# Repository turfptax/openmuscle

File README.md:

# 🧠 OpenMuscle (Legacy Repository)

> 📢 **NOTE:** This repository is no longer actively maintained.  
> All current work has moved to the new [**Open-Muscle GitHub Organization**](https://github.com/Open-Muscle).  
> Please see the new [OpenMuscle Hub](https://github.com/Open-Muscle/OpenMuscle-Hub) for the latest devices, firmware, and documentation.

---

## ⚡ Quick Links to New Repositories

| Project | Description | Link |
|--------|-------------|------|
| **OpenMuscle Hub** | Central documentation and overview for all OpenMuscle projects | [OpenMuscle-Hub](https://github.com/Open-Muscle/OpenMuscle-Hub) |
| **FlexGrid** | Modular 60-sensor wearable (successor to OM12) | [OpenMuscle-FlexGrid](https://github.com/Open-Muscle/OpenMuscle-FlexGrid) |
| **LASK5** | Labeling device with joystick and buttons | [OpenMuscle-LASK5](https://github.com/Open-Muscle/OpenMuscle-LASK5) |
| **Software** | MicroPython firmware, communication protocols, and ML hooks | [OpenMuscle-Software](https://github.com/Open-Muscle/OpenMuscle-Software) |
| **OM12 Legacy Band** | Historical 12-sensor band hardware | [OpenMuscle-Band](https://github.com/Open-Muscle/OpenMuscle-Band) |

---

## 🧬 About This Repo

This was the **original prototype** of OpenMuscle (OM12 + LASK4), developed to prove out muscle-based finger tracking using off-the-shelf parts and MicroPython.

It remains here for archival purposes and for those referencing:
- Early research and design iterations
- Press and academic mentions (42+ stars)
- Explorations in UDP-based muscle telemetry using hall effect sensors

<div align="center">
    
</div>

---

## 🧪 Prototype Overview

### 🧠 OM12 – OpenMuscle 12 Sensor Band (v5.3.0)

- 12 Hall Effect Sensors (49E)
- 6 Sensor Cells, dual-input
- PCB 5.3.0
- ESP32-S2
- MicroPython
- 1200 s/s via UDP transmission

### ✋ LASK4 (Legacy)

- 4 pistons
- 4 push buttons
- OLED screen
- ESP32-S2 Microcontroller

> The latest version is [LASK5](https://github.com/Open-Muscle/OpenMuscle-LASK5), with joystick and modular controls.

---

## ✅ Legacy Roadmap (Preserved for Context)

- [x] Create an open-source forearm bracelet (OM12)
- [x] Build a hand gesture labeling device (LASK4)
- [x] Create UDP-based data capture tool
- [ ] Build a hosted data training server
- [ ] Raise community awareness
- [ ] Create pre-production versions of both devices

---

## 🧾 License

This repo remains under the MIT License, but newer repositories may use the CERN-OHL-S v2.0 for hardware components. See the respective repos for details.

---

Made with 💡 by [@TURFPTAx](https://github.com/turfptax)  
Project now maintained at [Open-Muscle](https://github.com/Open-Muscle)

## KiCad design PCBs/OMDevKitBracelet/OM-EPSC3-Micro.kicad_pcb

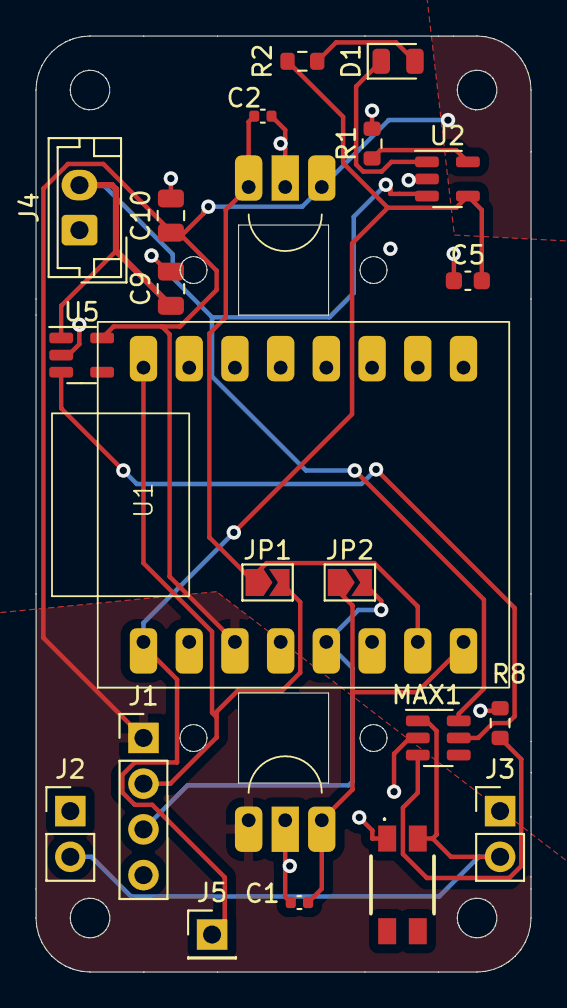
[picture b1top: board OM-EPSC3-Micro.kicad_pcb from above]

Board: 2 copper layers, 27.5 x 52.0 mm, 23 parts (0 on the bottom side), 14 nets.

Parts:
C1, C2: 100 nF; C_0402_1005Metric
C5: 2.2 uF; C_0603_1608Metric
C9, C10: 4.7uF; C_0805_2012Metric
D1: LED GREEN; LED_0805_2012Metric
H0, H1: A1369xUA-10; Hall49E
J1: Conn_01x04_Pin; PinHeader_1x04_P2.54mm_Vertical
J2, J3: Conn_01x02_Pin; PinHeader_1x02_P2.54mm_Vertical
J4: JST_02; JST_EH_B2B-EH-A_1x02_P2.50mm_Vertical
J5: Conn_01x01_Pin; PinHeader_1x01_P2.54mm_Vertical
JP1, JP2: SolderJumper_2_Open; SolderJumper-2_P1.3mm_Open_TrianglePad1.0x1.5mm
MAX1: SOT-23-6
R1: 2.7k; R_0603_1608Metric
R2: 150; R_0603_1608Metric
R8: 1K; R_0603_1608Metric
SW2: SW_Push; EVQP2P02M
U1: ESP32-C3-Super Mini
U2: LTC4054ES5-4.2; TSOT-23-5
U5: TPS7A03; SOT-23-5

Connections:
+3V3: C10.1, H0.1 (VCC), H1.1 (VCC), J1.1, U1.102 (3V3), U5.5 (OUT)
+3V8: C9.1, J4.1, MAX1.6 (Vcc), U2.3 (BAT), U5.1 (IN)
+5V: C5.2, J5.1, R2.1, U1.100 (5V), U2.4 (V_{CC})
ADC2: J1.3, JP2.2 (B), U1.3 (GPIO3)
ADC3: J1.2, JP1.2 (B), U1.5 (GPIO5)
GND: C1.1, C2.1, C5.1, C9.2, C10.2, H0.2 (GND), H1.2 (GND), J1.4, J2.1, J3.1, J4.2, MAX1.2 (GND), R1.2, R8.2, SW2.1, U1.101 (GND), U2.2 (GND), U5.2 (GND)
LDO_EN: MAX1.5 (OUT), U5.3 (EN)
unnamed: D1.2 (A), R2.2
unnamed: D1.1 (K), U2.1 (~CHRG)
unnamed: MAX1.3 (CLEAR), R8.1
unnamed: R1.1, U2.5 (PROG)
RMT-BTN: J2.2, J3.2, MAX1.1 (In), SW2.2
hall_0: C1.2, H0.3 (VOUT), JP2.1 (A), U1.0 (GPIO0)
hall_1: C2.2, H1.3 (VOUT), JP1.1 (A), U1.1 (GPIO1)

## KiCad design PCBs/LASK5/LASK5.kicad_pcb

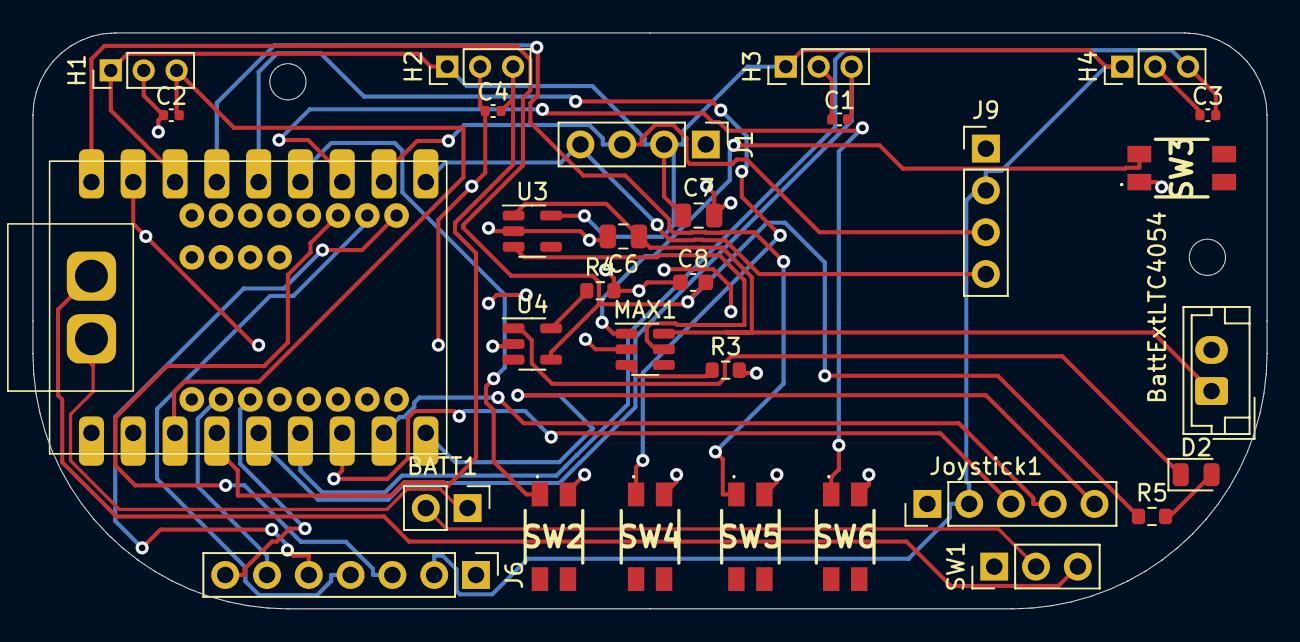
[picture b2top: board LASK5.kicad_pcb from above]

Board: 2 copper layers, 75.0 x 35.0 mm, 33 parts (0 on the bottom side), 31 nets.

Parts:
BATT1: Conn_01x02_Pin; PinHeader_1x02_P2.54mm_Vertical
BattExtLTC4054: JST_02; JST_EH_B2B-EH-A_1x02_P2.50mm_Vertical
C1, C2, C3, C4: 100 nF; C_0402_1005Metric
C6, C7: 4.7uF; C_0805_2012Metric
C8: 2.2 uF; C_0603_1608Metric
D2: LED GREEN; LED_0805_2012Metric
H1, H2, H3, H4: A1369xUA-10; PinHeader_1x03_P2.00mm_Vertical
H7, H8: MountingHole; MountingHole_2.2mm_M2
J1, J9: Conn_01x04; PinHeader_1x04_P2.54mm_Vertical
J6: Conn_01x07_Pin; PinHeader_1x07_P2.54mm_Vertical
Joystick1: Conn_01x05_Pin; PinHeader_1x05_P2.54mm_Vertical
MAX1: SOT-23-6
R3: 1K; R_0603_1608Metric
R4: 2.7k; R_0603_1608Metric
R5: 150; R_0603_1608Metric
SW1: SW_SPDT; PinHeader_1x03_P2.54mm_Vertical
SW2, SW3, SW4, SW5, SW6: SW_Push; EVQP2P02M
U1: ESP32-S3-Super Mini
U3: TPS7A03; SOT-23-5
U4: LTC4054ES5-4.2; TSOT-23-5

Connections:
+3V3: C7.1, H1.1 (VCC), H2.1 (VCC), H3.1 (VCC), H4.1 (VCC), J1.2, J6.2, J9.2, Joystick1.2, U1.103 (3V3), U3.5 (OUT)
+3V8: BattExtLTC4054.1, C6.1, MAX1.6 (Vcc), U3.1 (IN)
+5V: C8.2, R5.1, U1.105 (5V), U4.4 (V_{CC})
BPACK+: BATT1.2, SW1.2 (B)
BPACK-: BATT1.1, U1.384 (BAT-)
BPACKSW+: SW1.3 (C), U1.385 (BAT+)
GND: BattExtLTC4054.2, C1.1, C2.1, C3.1, C4.1, C6.2, C7.2, C8.1, H1.2 (GND), H2.2 (GND), H3.2 (GND), H4.2 (GND), J1.1, J6.1, J9.1, Joystick1.1, MAX1.2 (GND), R3.2, R4.2, SW2.2, SW3.1, SW4.2, SW5.2, SW6.2, U1.100 (GND), U3.2 (GND), U4.2 (GND)
GP14: J6.5, U1.14
GP15: J6.4, U1.15
GP16: J6.3, U1.16
GP46: J6.7, U1.46
GP47: J6.6, U1.47
JSW: Joystick1.5, U1.7 (GP7)
JX: Joystick1.3, U1.5 (GP5)
JY: Joystick1.4, U1.6 (GP6)
LDO_EN: MAX1.5 (OUT), U3.3 (EN)
unnamed: D2.2 (A), R5.2
unnamed: D2.1 (K), U4.1 (~CHRG)
unnamed: MAX1.3 (CLEAR), R3.1
unnamed: R4.1, U4.5 (PROG)
RMT-BTN: MAX1.1 (In), SW3.2
SCL: J1.3, J9.3, U1.9 (GP9)
SDA: J1.4, J9.4, U1.8 (GP8)
b_left: SW4.1, U1.12 (GP12)
b_right: SW5.1, U1.13 (GP13)
b_select: SW6.1, U1.10 (GP10)
b_start: SW2.1, U1.11 (GP11)
hall_0: C2.2, H1.3 (VOUT), U1.1 (GP1)
hall_1: C4.2, H2.3 (VOUT), U1.2 (GP2)
hall_2: C1.2, H3.3 (VOUT), U1.3 (GP3)
hall_3: C3.2, H4.3 (VOUT), U1.4 (GP4)

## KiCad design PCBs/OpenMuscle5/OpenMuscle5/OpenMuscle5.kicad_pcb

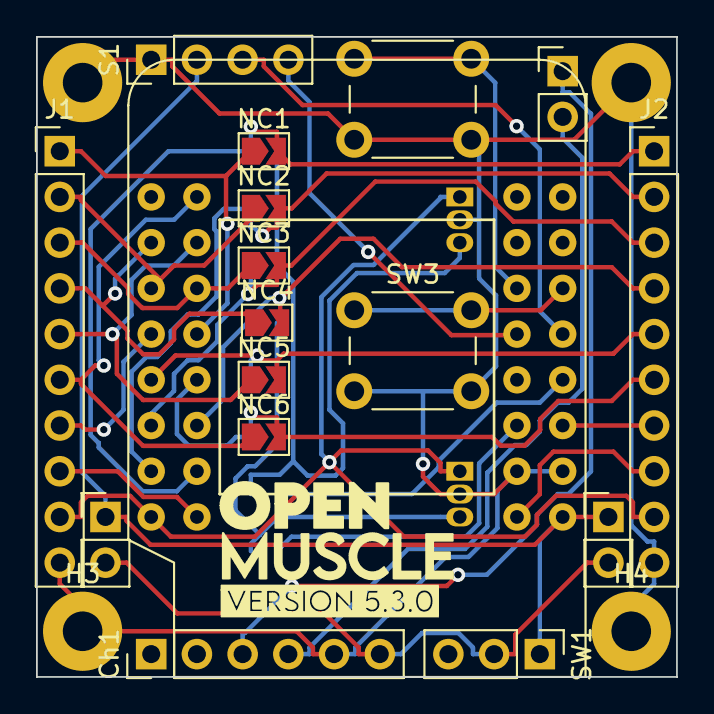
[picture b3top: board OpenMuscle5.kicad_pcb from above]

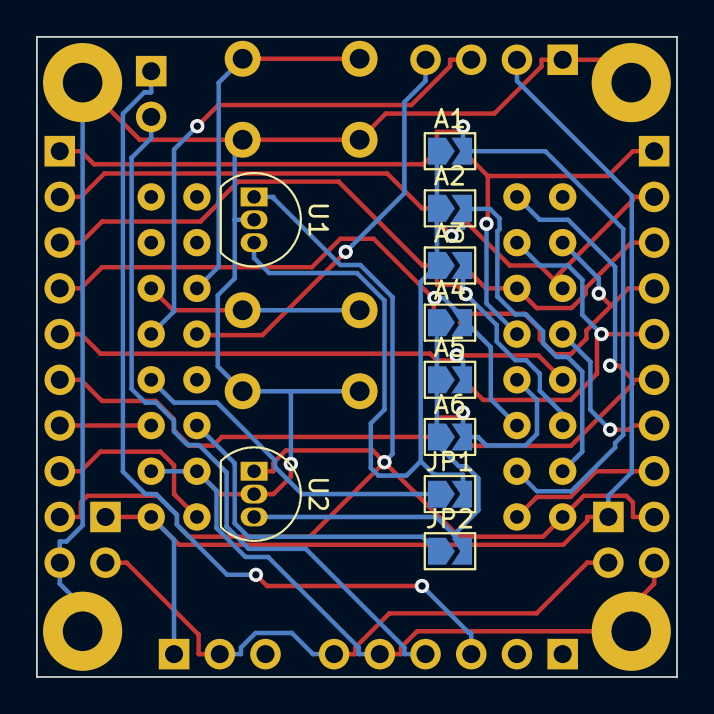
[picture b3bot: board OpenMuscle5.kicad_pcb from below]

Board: 2 copper layers, 35.6 x 35.6 mm, 31 parts (10 on the bottom side), 30 nets.

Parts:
A1, A2, A3, A4, A5, A6: SolderJumper_2_Open; SolderJumper-2_P1.3mm_Open_TrianglePad1.0x1.5mm
BT1: Conn_01x02_Male; PinHeader_1x02_P2.54mm_Vertical
Ch1: 3.7_Charge_MH_CD42; PinHeader_1x06_P2.54mm_Vertical
E1: ESP32-S2-Mini; ESP32-S2-mini
Five1, Five2: Conn_01x02_Male; PinHeader_1x02_P2.54mm_Vertical
H1, H2, H3, H4: MountingHole_Pad; MountingHole_2.2mm_M2_Pad
J1, J2: Head1x10-OMv5; PinHeader_1x10_P2.54mm_Vertical
JP1, JP2: SolderJumper_2_Open; SolderJumper-2_P1.3mm_Open_TrianglePad1.0x1.5mm
NC1, NC2, NC3, NC4, NC5, NC6: SolderJumper_2_Open; SolderJumper-2_P1.3mm_Open_TrianglePad1.0x1.5mm
S1: SSD1306; PinHeader_1x04_P2.54mm_Vertical
SW1: SW_SPST; PinHeader_1x03_P2.54mm_Vertical
SW2, SW3: SW_Push; SW_PUSH_6mm
U1, U2: DRV5033AJxLPG; TO-92_Inline

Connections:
unnamed: A1.1 (A), A2.1 (A), A3.1 (A), JP1.2 (B), U1.3 (OUT)
unnamed: A1.2 (B), E1.13 (ADC2_2), J2.1 (ACD0), NC1.2 (B)
unnamed: A2.2 (B), E1.12 (ADC2_1), J2.2 (ADC1), NC2.2 (B)
unnamed: A3.2 (B), E1.11 (ADC2_0), J2.3, NC3.2 (B)
unnamed: A4.1 (A), A5.1 (A), A6.1 (A), JP2.2 (B), U2.3 (OUT)
unnamed: A4.2 (B), E1.10 (ADC1_9), J2.4, NC4.2 (B)
unnamed: A5.2 (B), E1.9 (ADC1_8), J2.5, NC5.2 (B)
unnamed: A6.2 (B), E1.8 (ADC1_7), J2.6, NC6.2 (B)
unnamed: BT1.1, Ch1.3 (BAT-GND)
unnamed: BT1.2, Ch1.4 (BAT+)
unnamed: Ch1.6 (OUT-5V), Five1.2, Five2.2, SW1.2 (B)
unnamed: E1.1 (ADC1_0), J1.6, NC6.1 (A)
unnamed: E1.2 (ADC1_1), J1.5, NC5.1 (A)
unnamed: E1.3 (ADC1_2), J1.4, NC4.1 (A)
unnamed: E1.4 (ADC1_3), J1.3, NC3.1 (A)
unnamed: E1.5 (ADC1_4), J1.2 (ADC1), NC2.1 (A)
unnamed: E1.6 (ADC1_5), J1.1 (ACD0), NC1.1 (A)
unnamed: E1.7 (ADC1_6), J1.7
unnamed: E1.14 (ADC2_3), J1.8
unnamed: E1.15 (ADC2_4), J2.8
unnamed: E1.16 (ADC2_5), J2.7
unnamed: E1.17 (ADC2_6), JP2.1 (A)
unnamed: E1.18 (ADC2_7), JP1.1 (A)
unnamed: E1.33 (FSPI_HD_io4), S1.3 (SCL)
unnamed: E1.34 (FSPI_SCO_dqs), S1.4 (SDA)
unnamed: E1.35 (FSPI_D_io6), SW3.1
unnamed: E1.36 (FSPI_CLK_io7), SW2.1
unnamed: E1.133 (3.3V), J1.9, J2.9, U1.1 (VCC), U2.1 (VCC)
unnamed: E1.150 (VBUS), Five1.1, Five2.1, S1.2 (VCC), SW1.1 (A)
unnamed: Ch1.5 (OUT-GND), E1.129 (GND), E1.130 (GND), H1.1, H2.1, H3.1, H4.1, J1.10, J2.10, S1.1 (GND), SW2.2, SW3.2, U1.2 (GND), U2.2 (GND)

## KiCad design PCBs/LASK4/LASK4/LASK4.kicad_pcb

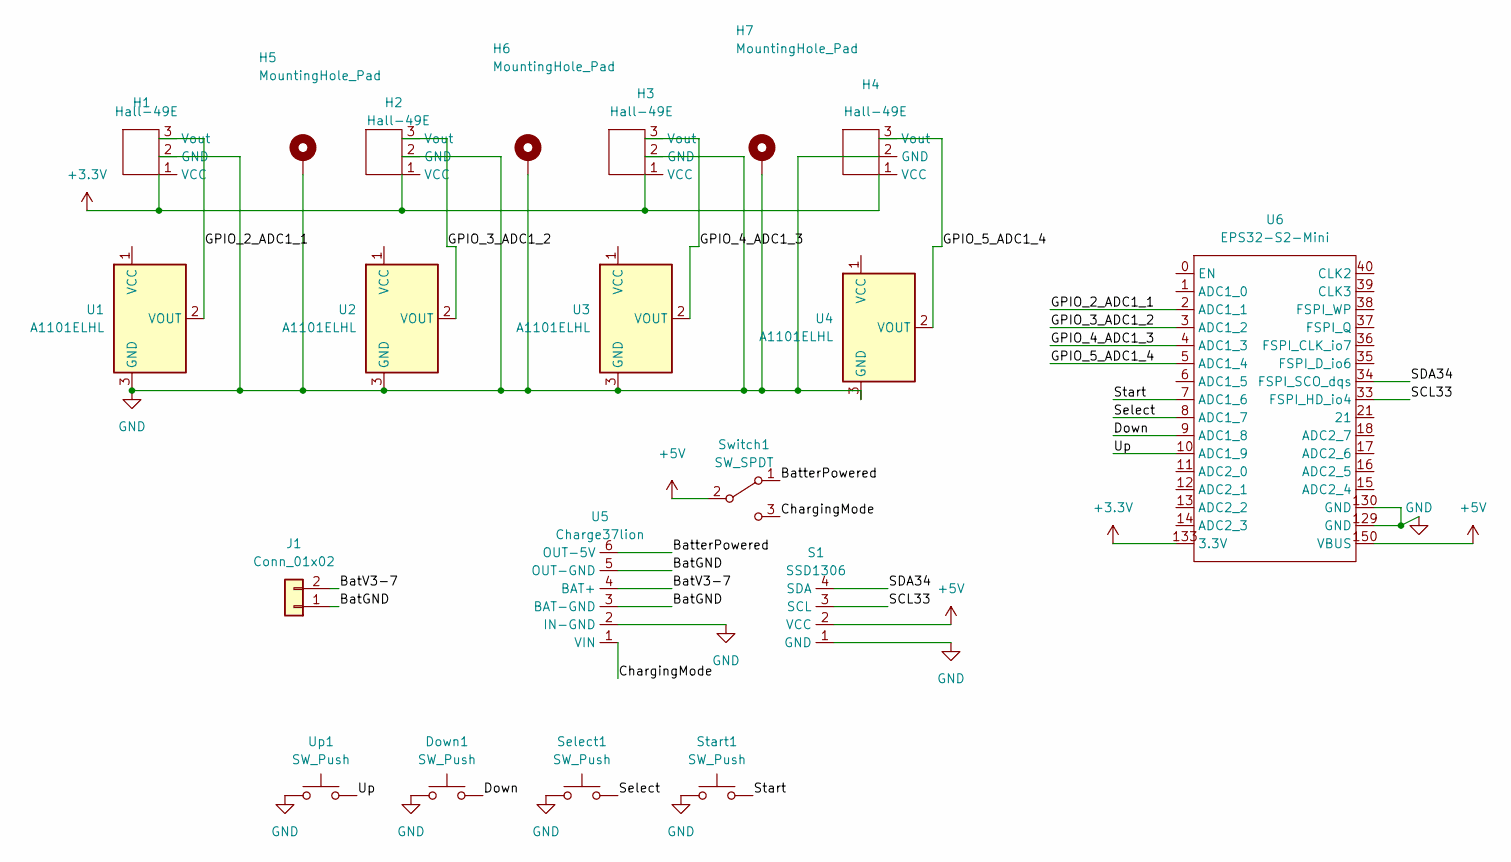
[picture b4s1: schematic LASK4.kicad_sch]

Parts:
Down1: SW_Push; SW_PUSH_6mm
H1, H2, H3, H4: Hall-49E; PinHeader_1x03_P2.00mm_Vertical
H5, H6, H7: MountingHole_Pad; MountingHole_2.2mm_M2_DIN965_Pad
J1: Conn_01x02; PinHeader_1x02_P2.54mm_Vertical
S1: SSD1306; PinHeader_1x04_P2.54mm_Vertical
Select1: SW_Push; SW_PUSH_6mm
Start1: SW_Push; SW_PUSH_6mm
Switch1: SW_SPDT; PinHeader_1x03_P2.54mm_Vertical
U1, U2, U3, U4: A1101ELHL; SOT-23W
U5: Charge37lion; PinHeader_1x06_P2.54mm_Vertical
U6: EPS32-S2-Mini; ESP32-S2-Mini
Up1: SW_Push; SW_PUSH_6mm

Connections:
+3.3V: H1.1 (VCC), H2.1 (VCC), H3.1 (VCC), H4.1 (VCC), U6.133 (3.3V)
+5V: S1.2 (VCC), Switch1.2 (B), U6.150 (VBUS)
/BatGND: J1.1, U5.3 (BAT-GND), U5.5 (OUT-GND)
/BatV3-7: J1.2, U5.4 (BAT+)
/BatterPowered: Switch1.1 (A), U5.6 (OUT-5V)
/ChargingMode: Switch1.3 (C), U5.1 (VIN)
/Down: Down1.2, U6.9 (ADC1_8)
/GPIO_2_ADC1_1: H1.3 (Vout), U1.2 (VOUT), U6.2 (ADC1_1)
/GPIO_3_ADC1_2: H2.3 (Vout), U2.2 (VOUT), U6.3 (ADC1_2)
/GPIO_4_ADC1_3: H3.3 (Vout), U3.2 (VOUT), U6.4 (ADC1_3)
/GPIO_5_ADC1_4: H4.3 (Vout), U4.2 (VOUT), U6.5 (ADC1_4)
/SCL33: S1.3 (SCL), U6.33 (FSPI_HD_io4)
/SDA34: S1.4 (SDA), U6.34 (FSPI_SCO_dqs)
/Select: Select1.2, U6.8 (ADC1_7)
/Start: Start1.2, U6.7 (ADC1_6)
/Up: U6.10 (ADC1_9), Up1.2
GND: Down1.1, H1.2 (GND), H2.2 (GND), H3.2 (GND), H4.2 (GND), H5.1, H6.1, H7.1, S1.1 (GND), Select1.1, Start1.1, U1.3 (GND), U2.3 (GND), U3.3 (GND), U4.3 (GND), U5.2 (IN-GND), U6.129 (GND), U6.130 (GND), Up1.1

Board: 2 copper layers, 20 parts (1 on the bottom side), 17 nets, no tracks yet.

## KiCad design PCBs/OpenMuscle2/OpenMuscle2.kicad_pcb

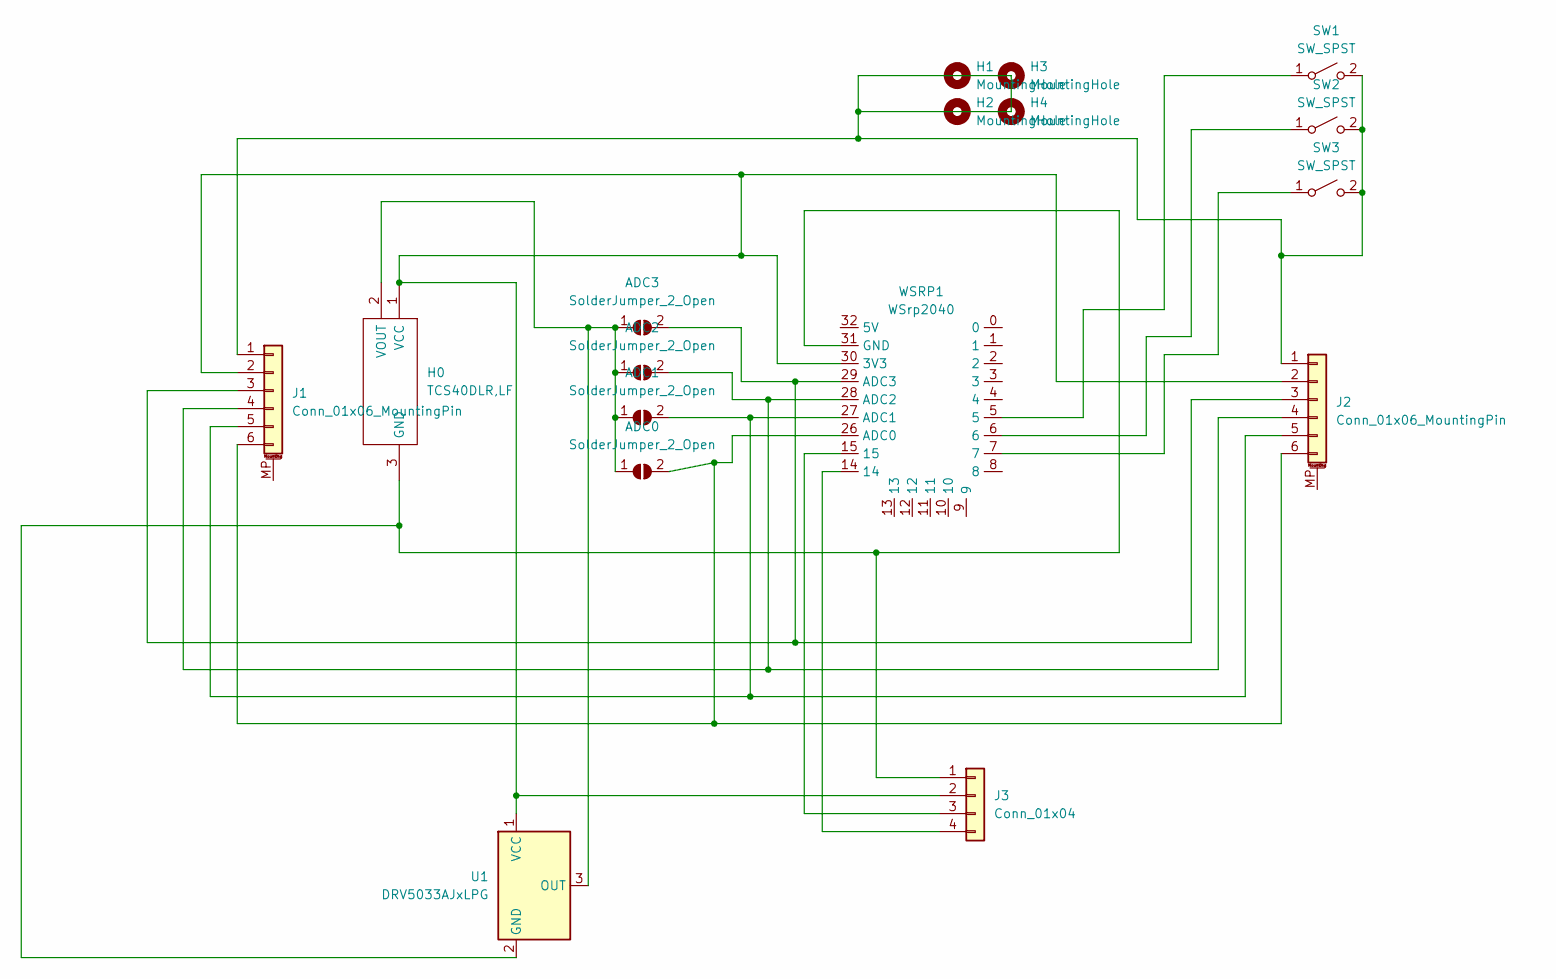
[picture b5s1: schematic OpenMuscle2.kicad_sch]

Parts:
ADC0, ADC1, ADC2, ADC3: SolderJumper_2_Open; SolderJumper-2_P1.3mm_Open_TrianglePad1.0x1.5mm
H0: TCS40DLR,LF; SOTFL95P240X88-3N; Manufacturer_Part_Number TCS40DLR,LF; Mouser Part Number 757-TCS40DLRLF
H1, H2, H3, H4: MountingHole; MountingHole_2.2mm_M2_DIN965_Pad
J1, J2: Conn_01x06_MountingPin; PinHeader_1x06_P2.54mm_Vertical
J3: Conn_01x04; PinHeader_1x04_P2.54mm_Vertical
SW1, SW2, SW3: SW_SPST; SW_PUSH_6mm
U1: DRV5033AJxLPG; TO-92_Inline
WSRP1: WSrp2040; WSRP2040

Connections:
unnamed: H0.1 (VCC), J1.2, J2.2, J3.2, U1.1 (VCC), WSRP1.30 (3V3)
unnamed: ADC0.1 (A), ADC1.1 (A), ADC2.1 (A), ADC3.1 (A), H0.2 (VOUT), U1.3 (OUT)
unnamed: H0.3 (GND), J3.1, U1.2 (GND), WSRP1.31 (GND)
unnamed: J1.1, J2.1, SW1.2 (B), SW2.2 (B), SW3.2 (B)
unnamed: ADC3.2 (B), J1.3, J2.3, WSRP1.29 (ADC3)
unnamed: ADC2.2 (B), J1.4, J2.4, WSRP1.28 (ADC2)
unnamed: ADC1.2 (B), J1.5, J2.5, WSRP1.27 (ADC1)
unnamed: ADC0.2 (B), J1.6, J2.6, WSRP1.26 (ADC0)
unnamed: SW1.1 (A), WSRP1.5
unnamed: SW2.1 (A), WSRP1.6
unnamed: SW3.1 (A), WSRP1.7
unnamed: J3.4, WSRP1.14
unnamed: J3.3, WSRP1.15

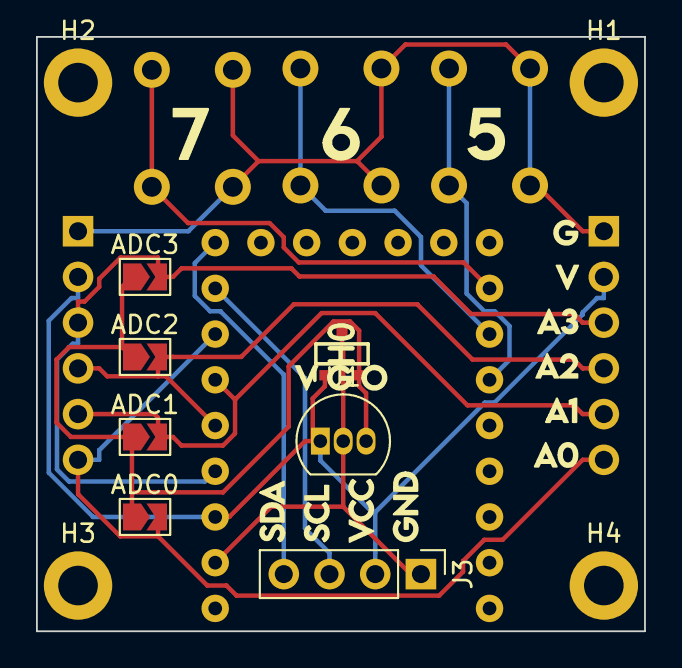
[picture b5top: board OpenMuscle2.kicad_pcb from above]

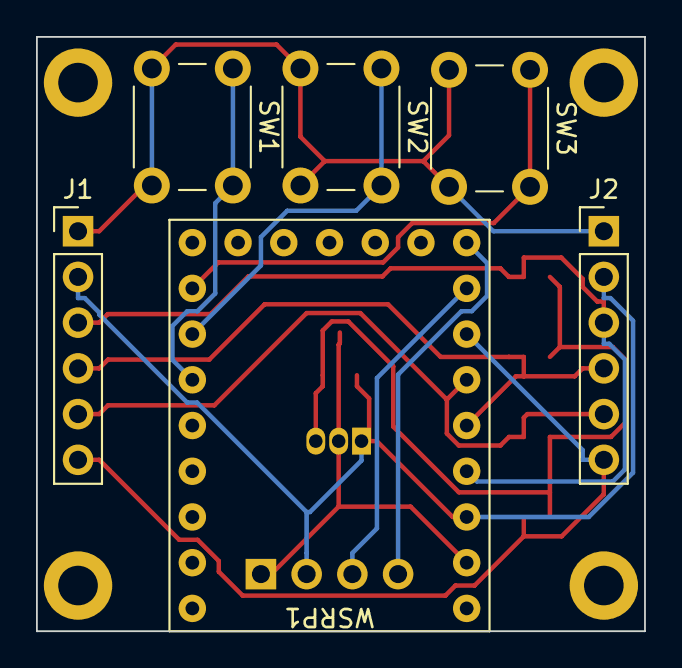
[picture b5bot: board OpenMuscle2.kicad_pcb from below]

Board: 2 copper layers, 33.8 x 33.0 mm, 17 parts (6 on the bottom side), 13 nets.

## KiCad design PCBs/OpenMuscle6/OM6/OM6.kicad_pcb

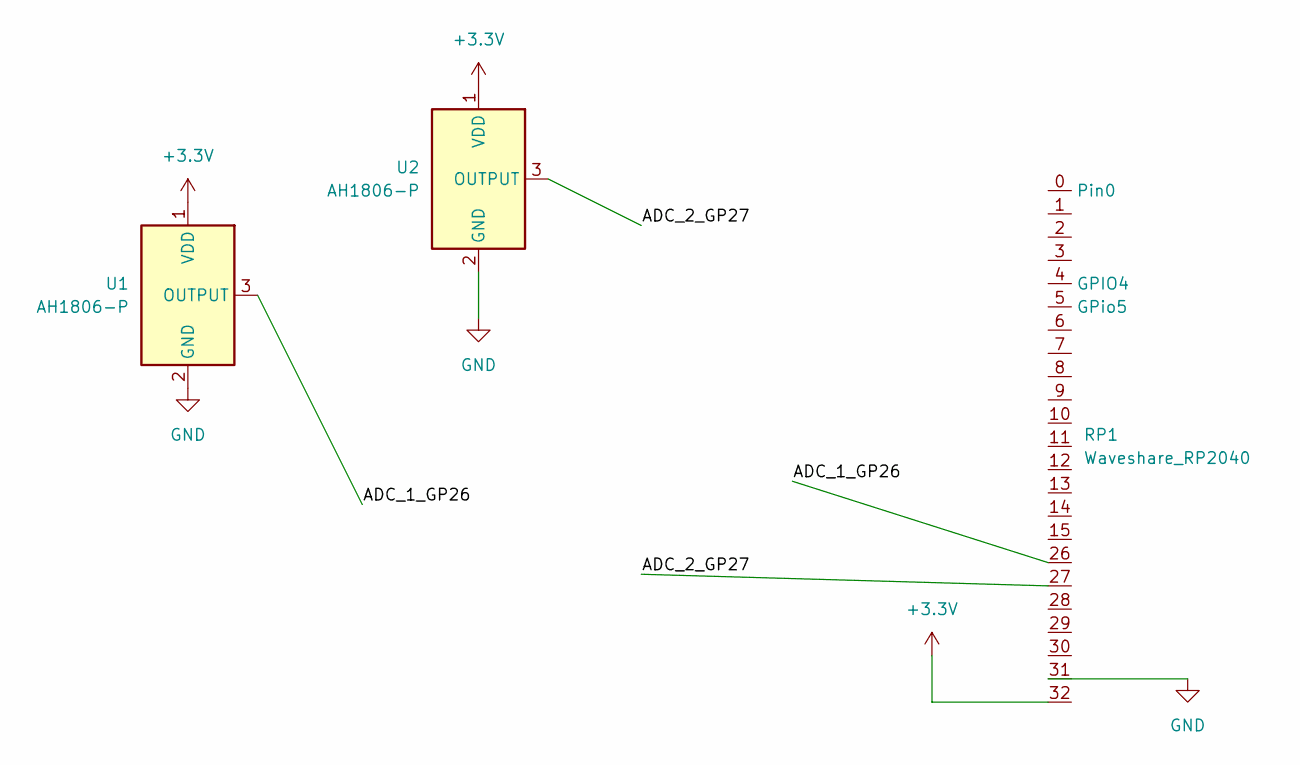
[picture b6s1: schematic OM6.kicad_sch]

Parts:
RP1: Waveshare_RP2040; RP2040-Zero
U1, U2: AH1806-P; JST_EH_B3B-EH-A_1x03_P2.50mm_Vertical

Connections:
+3.3V: RP1.32, U1.1 (VDD), U2.1 (VDD)
/ADC_1_GP26: RP1.26, U1.3 (OUTPUT)
/ADC_2_GP27: RP1.27, U2.3 (OUTPUT)
GND: RP1.31, U1.2 (GND), U2.2 (GND)

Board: 2 copper layers, 3 parts (0 on the bottom side), 4 nets, no tracks yet.

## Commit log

2022-08-30 Create License
    Open GNU license for free distribution of this software for everyone
2022-08-30 Create COPYING
2022-08-30 Create componentSEARCH
2022-08-31 Update componentSEARCH
2022-09-03 MainCell0Upload
    Updated Project with main comp file structure
2022-09-07 Cello-Compute-Gerber
    Gerber files for the Cello Compute module
2022-09-07 Update Components
    Components link added.
2022-09-07 CELL0 Gerber Files Added
2022-10-10 Updated boot
2022-10-10 created open muscle wireless access point
2022-10-19 PCB update
    Need to organize but I'm behind on my documentation. Here are the current PCBs gerber files and others.
2022-10-19 Update Readme file
    Updated components and adjustments to readme
2022-10-19 Going from ESP32-C3 wifi to external
2022-10-19 Update main boot.py file
2022-10-19 Delete ESP32-S2-OM-Boot.py
    Remove older boot file for OpenMuscle band
2022-10-19 New boot for open muscle
2022-10-19 STL file upload
    Need a lot better naming convention :
2022-11-05 BackupUploads
    UPloadbakcup py files for esp32-s2 and ssd1306
2022-11-06 micropython update
    Updated the micropython folder to include the most up to date upython code for Open Muscle 5.3.0 or 5.4.0
2022-11-07 boot updated
    micropython boot update
2022-11-07 remove non-forked
    removed items that are needed to be forked
2022-11-10 Create UDPserver.py
    The placeholder for the UDP server on the network client/server side.
2022-11-22 MAJOR update
    a
2022-11-26 urepl update
    Updated UREPL and UDP server modules
2022-12-01 updated information
    Changes to the design 5.3.0 updated
2022-12-25 Culled Files
    Culled files
2022-12-27 removed
2023-01-01 openhand
    openhand boot update
2023-01-02 collectmuscle
    first LASK plus Band capture
2023-01-08 Training File 15 and live stream
    Check twitch for video livestream of this data capture 1-8-2023
2023-01-08 data 16 and 17
    1-8-2023
2023-01-08 20 The fist success
    training_file20.txt has both LASK and OM-Band12v5 data together with video on twitch
2023-01-11 collectmuscle GUI
    Added GUI for collectmuscle.py
2023-01-11 GUI update
    GUI update
2023-01-12 minor update overhaul
    minor update overhaul
    # Pinout Uploads
    # STL file adjustments
    # Training Data testing
    # Lask System Upload
    ## Major revisions coming back to back as we enter in a new phase in development.
2023-01-13 Good Data
2023-01-16 1 Before This decent data
    Needed to update some UDP code and boot.py
2023-01-18 Woot Woot
    12X1 is functional!
2023-01-18 Good Training Data
    Good Training Data
2023-01-19 ML start
    Machine Learning Phase Started
2023-01-20 data matching for ml
    updated txt2csv to make it take files from recorded text file to csv for machine learning. Most likely a temp process needs to be streamlined later.
2023-01-20 First Clean Data
2023-01-29 Major Update
2023-01-30 LASK4 Update
    Updated LASK4 PCB and pertaining documents.
2023-02-03 LASK4-1
2023-02-18 LASK4
    Updates
2023-02-20 LASK4V2
2023-03-01 ML Learning & Virt Env
2023-03-01 dodec
2023-03-11 Lask4v2 Update
2023-03-15 OM12
2023-03-16 Major Update OM12
    Major Update To isolate only the current working version from all the others.
2023-03-16 OM12 V7 Update
    OM12 7 is the latest and yet to be built prototype
2023-03-16 Updated Roadmap
2023-03-16 Update README.md
    OM24 Suggested Features Roadmap
2023-03-16 OM12 Working Prototype Proof of Concept
    OM12 Major update includes all files for the working proof-of-concept of OpenMuscle12 also referred to as OM5.3.0
    UDP Server for collecting data from LASK4 and OM12
    Basic Packet Matching txt2csv.py python function
    Overall Basic Functionality of Hardware and Software
    Machine Learning Not Yet Started
2023-03-16 Decent Captured Data
2023-03-16 MimicOMData
2023-03-17 Image-update
    Update Description and Images for OM12 5.3.0
2023-03-25 Machine Learning Update
    Got the machine learning process to work and display in close to real-time
2023-03-26 OM Machine Learning Data
    Backup of the Raw data to train the Random Forest Regressor shown on the latest update on openmuscle.org 3-26-2023
    # Wanted to include both the january and march dataset.
2023-03-28 Machine Learning Update
    Includes link to the shared model and all the code to predict live sensor output and create predicted output CSV.
2023-03-29 Live Training with only 5 min of data files :D
    Uploaded a video where I trained the data and had it predict in real-time. These are the adjustments made for that video.
2023-03-31 Demo Files
2023-04-01 Demo Update
2023-04-01 Major Org Update
2023-04-02 Demo Initial Tests
2023-04-02 NewSet
2023-04-02 Included Time Domain or Slope
2023-04-02 time_domain_slope
2023-04-02 Demo 4-2-23
2023-04-02 Updated Names
2023-04-03 added Hari's hand to my demo code
    Hari Wiguna helped to get the hand code ready for the demo. Thank you so much Hari!! Could not have demoed this without you!
2023-04-03 Live Demo Updates
    Updated some files to show the whole process live.
    Capture Raw signals from LASK and Open Muscle
    Convert Capture into CSV
    Train Model From CSV
    Predict Live Data From Open Muscle!
2023-04-03 live update 2
2023-04-03 demo update 3
2023-04-06 Added submodule ugit
2023-04-16 January 23 Data Files for Training Update
    https://openmuscle.org/finger-movement-recognition-using-radial-pressure-sensors-on-the-forearm-and-machine-learning-techniques/
2023-04-16 Other Datasets
    These datasets show a great accuracy result from Random Forest Regressor. January23 was the most accurate and used OM12 5.3.0 hardware and PCB.
2023-04-16 Demo Predictions for Jan23 Dataset
    Includes training file to look at the largest dataset: January23
2023-04-19 Demo Organize
    Organized Demo Files
2023-04-19 Images and Diagrams
2023-04-19 om12 clevis stl
2023-05-07 Update License
    The GNU License might not be applicable since the MicroPython code was used. The MIT license has been applied instead to allow for the code to fall under the requirements.
2023-08-18 requirements update
    Adding requirements for python.
2024-10-24 LASK5 DevKit
2024-10-24 OMDevKitBracelet
2024-10-24 OMDevKitSTL
2024-10-24 Added uLabel depressor
    See Ultimate Robotics uMyo and uLabel for more info.
